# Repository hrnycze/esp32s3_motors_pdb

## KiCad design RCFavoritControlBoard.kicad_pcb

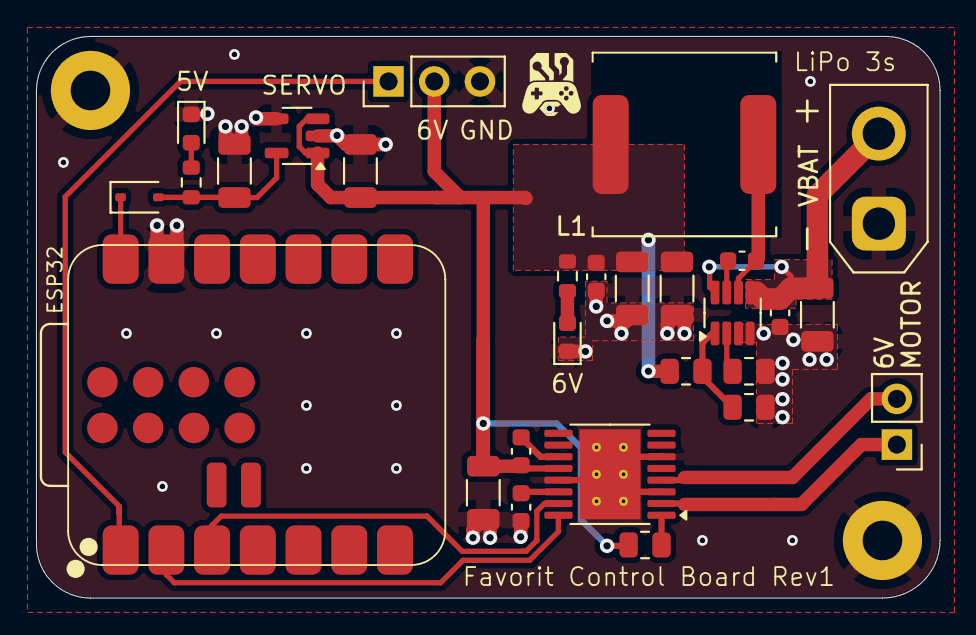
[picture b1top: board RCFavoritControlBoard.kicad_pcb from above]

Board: 2 copper layers, 50.2 x 31.2 mm, 30 parts (0 on the bottom side), 19 nets.

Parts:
5V: BLUE; LED_0603_1608Metric
C1: 10nF; C_0603_1608Metric
C2, C8, C9: 10uF/25V; C_1206_3216Metric
C3, C6: 100nF/25V; C_0603_1608Metric
C4, C5: 22uF/16V; C_1206_3216Metric
C7: 10uF; C_1206_3216Metric
C10: 10nF/16V; C_0603_1608Metric
C11: 2.2uF/6.3A; C_0603_1608Metric
D1: BLUE; LED_0603_1608Metric
D3: 1N5819WS; D_SOD-323
ESP32: XIAO-ESP32-S3-SMD; XIAO-ESP32S3-SMD
H1, H2: MountingHole_Pad; MountingHole_2.2mm_M2_Pad
J3: Conn_01x03_Pin; PinHeader_1x03_P2.54mm_Vertical
L1: 5.2uH; L_SOREDE_SNR.1050_10x10x5mm
MOTOR: Screw_Terminal_01x02; PinHeader_1x02_P2.54mm_Vertical
R1, R3: 200k; R_0805_2012Metric
R2, R5: 1k; R_0603_1608Metric
R4, R6: 22k1; R_0805_2012Metric
U1: SY8303; TSOT-23-8
U2: TPS7A20xxxPDBVR; SOT-23-5
U3: DRV8833PWP; HTSSOP-16-1EP_4.4x5mm_P0.65mm_EP3.4x5mm_Mask2.46x2.31mm_The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
VBAT: Screw_Terminal_01x02; AMASS_XT30UPB-M_1x02_P5.0mm_Vertical

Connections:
+5V: C9.1, D3.2 (A), R5.1, U2.5 (OUT)
+6V: C4.1, C5.1, C6.1, C7.1, C8.1, C10.1, J3.2, L1.2, R1.1, R2.1, R6.1, U2.1 (IN), U2.3 (EN), U3.12 (VM)
DRV8833_IN1: ESP32.2 (GPIO2_A1_D1), U3.16 (AIN1)
DRV8833_IN2: ESP32.3 (GPIO3_A2_D2), U3.15 (AIN2)
GND: 5V.1 (K), C2.2, C3.2, C4.2, C5.2, C6.2, C7.2, C8.2, C9.2, C11.2, D1.1 (K), ESP32.13 (GND), H1.1, H2.1, J3.3, R3.2, R4.2, U1.3 (GND), U1.4 (GND), U2.2 (GND), U2.4 (NC), U3.3 (AISEN), U3.6 (BISEN), U3.13 (GND), U3.17 (GND), VBAT.1
Motor+: MOTOR.1, U3.2 (AOUT1)
Motor-: MOTOR.2, U3.4 (AOUT2)
unnamed: D1.2 (A), R2.2
unnamed: 5V.2 (A), R5.2
unnamed: D3.1 (K), ESP32.14 (5V)
unnamed: C1.2, U1.7 (BS)
unnamed: R1.2, R4.1, U1.1 (FB)
unnamed: R3.1, U1.2 (FS)
unnamed: C1.1, L1.1, U1.6 (LX)
unnamed: C10.2, U3.11 (VCP)
unnamed: C11.1, U3.14 (VINT)
unnamed: R6.2, U3.1 (~SLEEP)
SERVO_PWM: ESP32.1 (GPIO1_A0_D0), J3.1
VBAT: C2.1, C3.1, U1.5 (IN), U1.8 (EN), VBAT.2

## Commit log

2025-05-03 before routing
2025-05-04 routing done
2025-05-09 GND is filled in top layer
2025-05-09 tried to use Fabrication Toolkit for JLCPCB
2025-05-13 added logo
